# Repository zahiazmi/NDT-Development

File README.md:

# NDT-Development

The purpose of this project is to generate a single high voltage DC pulse with specific pulse period and width. The system requirements are

1. High DC amplitude 150V
2. Low voltage input 5-12V
3. Lowest pulse widht 200 ns
4. Low transient time

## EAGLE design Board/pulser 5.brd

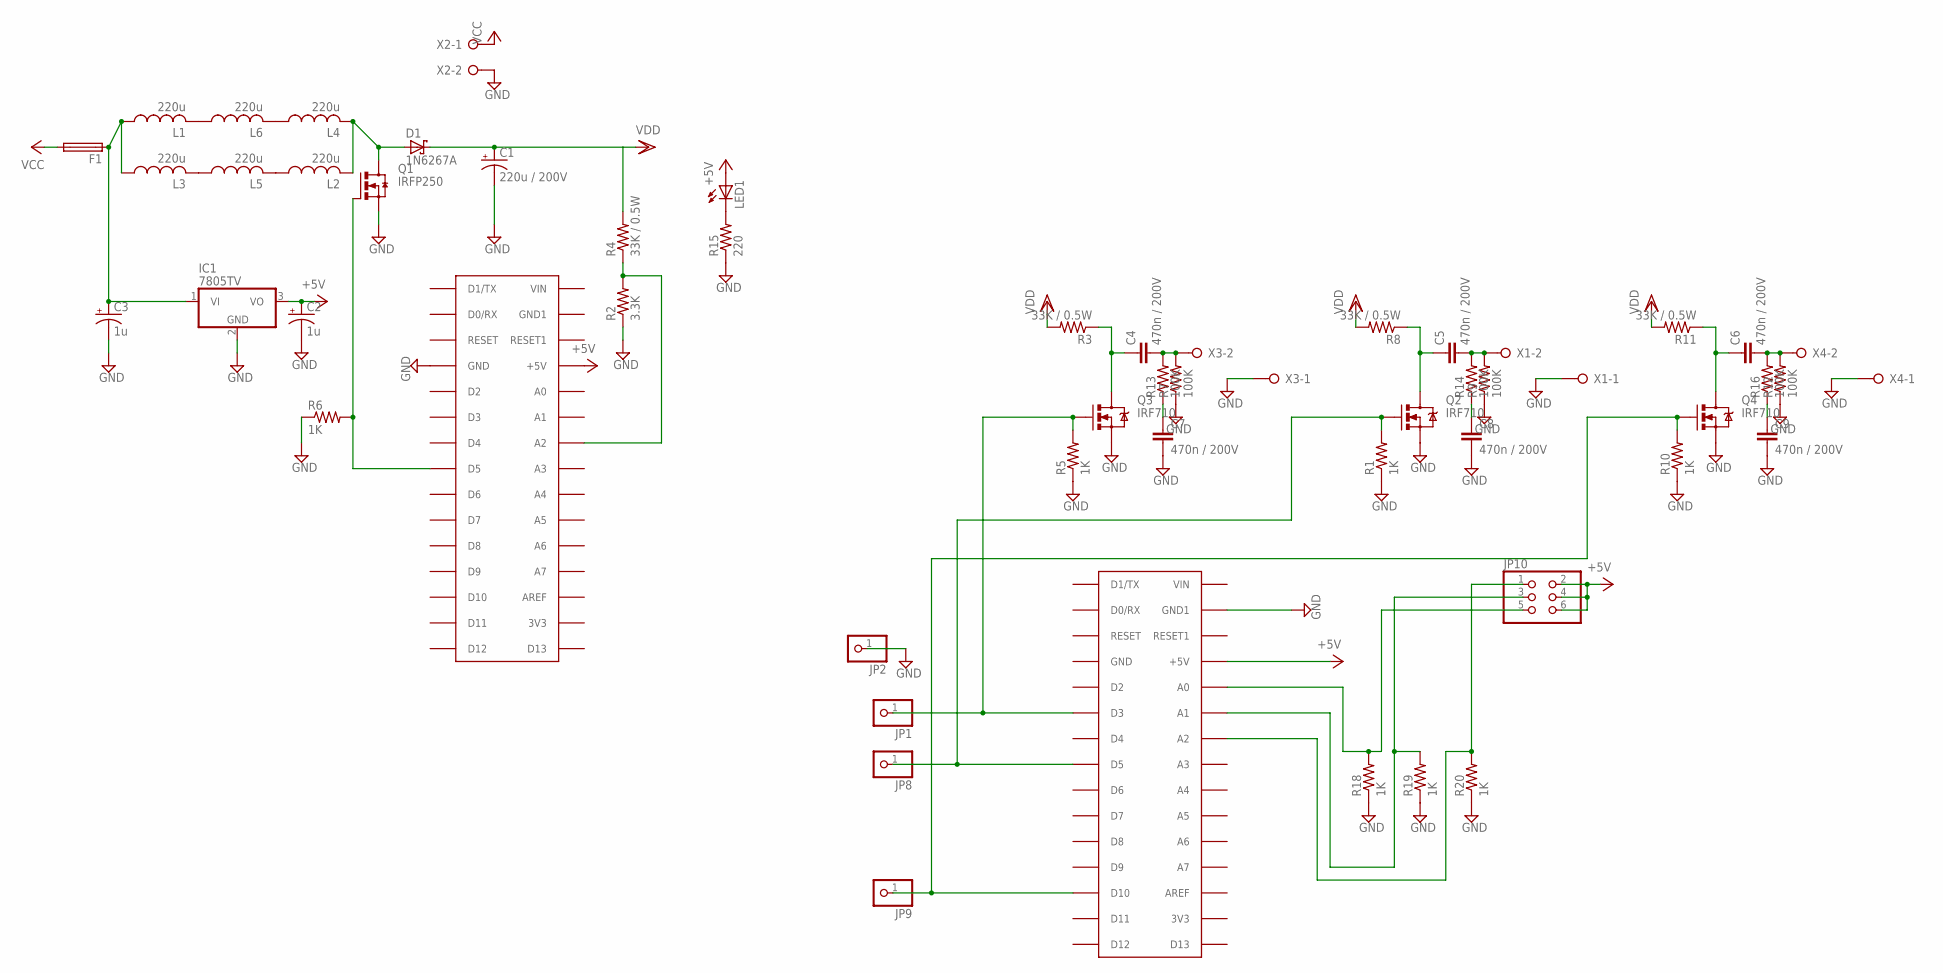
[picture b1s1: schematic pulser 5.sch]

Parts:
C1: 220u / 200V; E7,5-18
C2, C3: 1u; E2,5-6
C4, C5, C6, C7, C8, C9: 470n / 200V; C150-064X183
D1: 1N6267A; C4111-15
F1: TE5
IC1: 7805TV; TO220V
JP1, JP2, JP8, JP9: PINHD-1X1; 1X01
JP10: PINHD-2X3; 2X03
L1, L2, L3, L4, L5, L6: 220u; LAP02KR
LED1: LED5MM
Q1: IRFP250; TO-247AD-V
Q2, Q3, Q4: IRF710; TO220V
R1, R5, R6, R10, R18, R19, R20: 1K; 0207/10
R2: 3.3K; 0207/10
R3, R4, R8, R11: 33K / 0.5W; 0309/12
R7, R9, R12, R13, R14, R16: 100K; 0207/10
R15: 220; 0207/10
U$1, U$2: ARDUINONANO; PDIP-32
X1, X2, X3, X4: W237-02P; W237-132

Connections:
+5V: C2.+, IC1.3 (VO), JP10.2, JP10.4, JP10.6, LED1.A, U$1.+5V, U$2.+5V
GND: C1.-, C2.-, C3.-, C7.2, C8.2, C9.2, IC1.2 (GND), JP2.1, Q1.S, Q2.3 (S), Q3.3 (S), Q4.3 (S), R1.1, R2.1, R5.1, R6.1, R7.1, R9.1, R10.1, R12.1, R15.1, R18.1, R19.1, R20.1, U$1.GND, U$2.GND1, X1.1, X2.2, X3.1, X4.1
unnamed: C3.+, F1.1, IC1.1 (VI), L1.1, L3.1
unnamed: D1.A, L2.2, L4.2, Q1.D
unnamed: C4.1, Q3.2 (D), R3.1
unnamed: JP1.1, Q3.1 (G), R5.2, U$2.D3
unnamed: C4.2, R7.2, R13.2, X3.2
unnamed: LED1.K (C), R15.2
unnamed: R2.2, R4.1, U$1.A2
unnamed: L3.2, L5.1
unnamed: Q1.G, R6.2, U$1.D5
unnamed: C5.1, Q2.2 (D), R8.1
unnamed: L4.1, L6.2
unnamed: JP8.1, Q2.1 (G), R1.2, U$2.D5
unnamed: JP9.1, Q4.1 (G), R10.2, U$2.D10
unnamed: C5.2, R9.2, R14.2, X1.2
unnamed: C6.1, Q4.2 (D), R11.1
unnamed: C7.1, R13.1
unnamed: JP10.5, R18.2, U$2.A0
unnamed: L2.1, L5.2
unnamed: C6.2, R12.2, R16.2, X4.2
unnamed: C8.1, R14.1
unnamed: L1.2, L6.1
unnamed: C9.1, R16.1
unnamed: JP10.3, R19.2, U$2.A1
unnamed: JP10.1, R20.2, U$2.A2
VCC: F1.2, X2.1
VDD: C1.+, D1.C, R3.2, R4.2, R8.2, R11.2

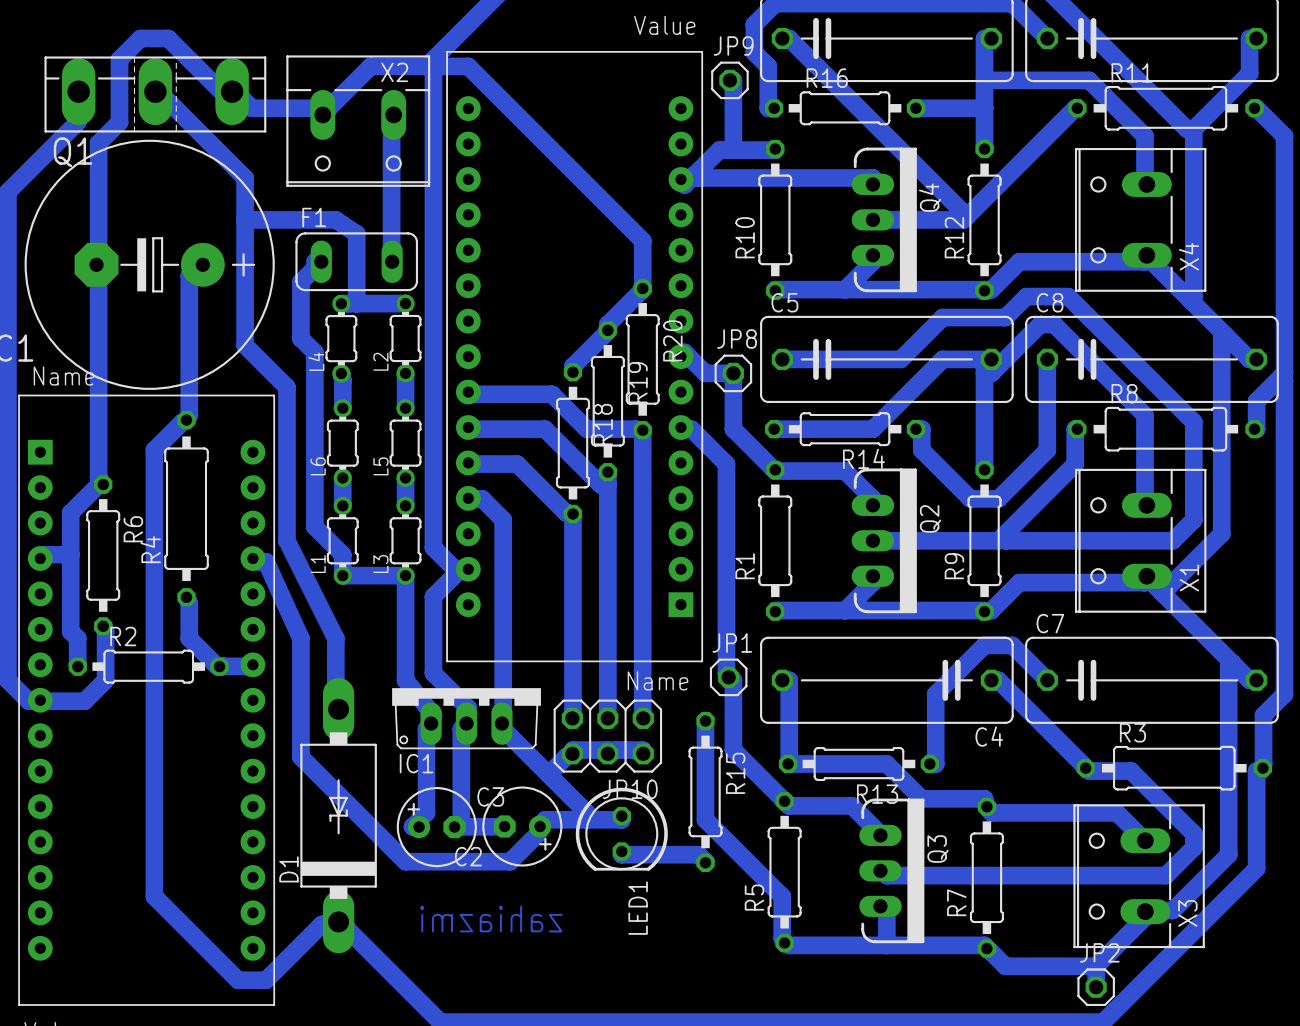
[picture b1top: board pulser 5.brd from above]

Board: 2 copper layers, 53 parts (0 on the bottom side), 28 nets.

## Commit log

2018-12-01 Worked Version 1
    Worked Version 1

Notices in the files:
parts and their libraries:
SparkFun-DiscreteSemi: Licensing: Creative Commons ShareAlike 4.0 International - https://creativecommons.org/licenses/by-sa/4.0
